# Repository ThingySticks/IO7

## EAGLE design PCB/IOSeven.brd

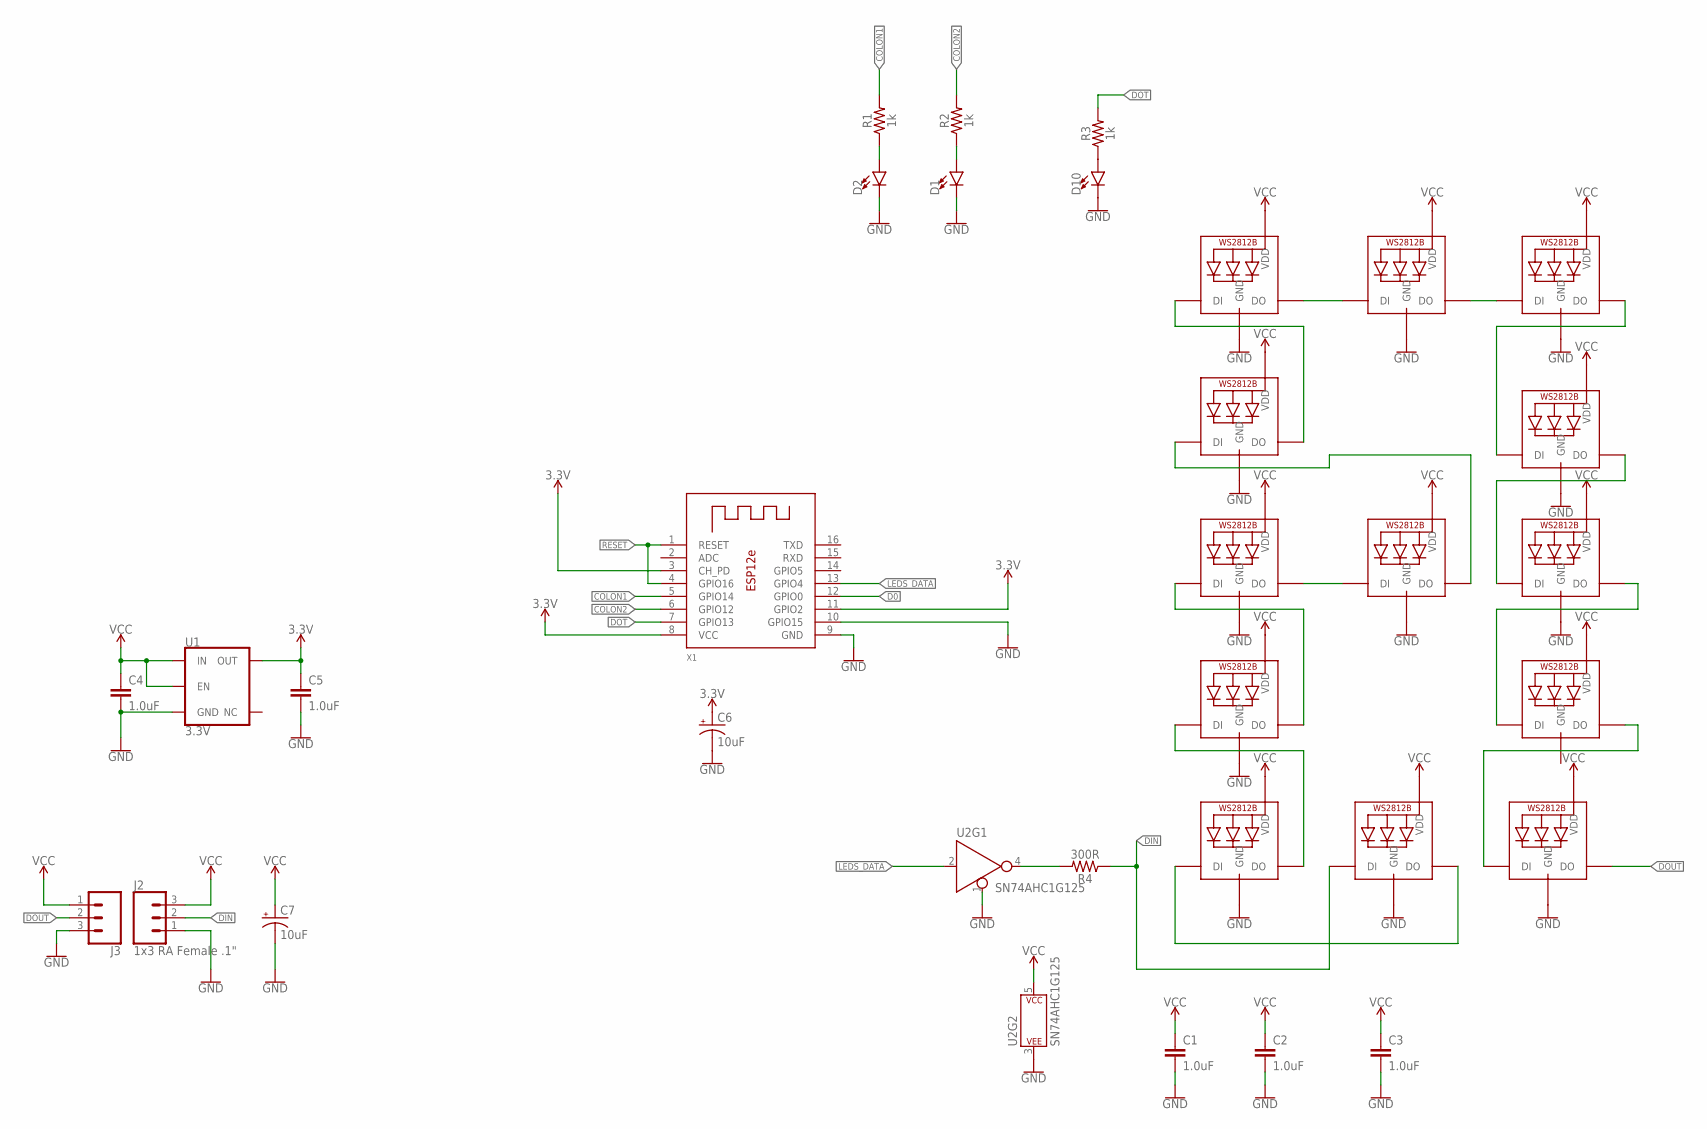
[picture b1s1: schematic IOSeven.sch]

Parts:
C1, C2, C3, C4, C5: 1.0uF; 0603
C6, C7: 10uF; 0603-POLAR
D1, D2, D10: LED0603; LED-0603
J2: 1x3 RA Female .1"; 1X03_SMD_RA_FEMALE
J3: CONN_03SMD_RA_MALE; 1X03_SMD_RA_MALE
LED17, LED18, LED19, LED20, LED21, LED22, LED23, LED24, LED25, LED26, LED27, LED28, LED29: WS2812B3535; LED3535
R1, R2, R3: 1k; 0603
R4: 300R; 0603
U1: 3.3V; SOT23-5
U2: SN74AHC1G125; SOT23-5
X1: ESP-12E

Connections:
3.3V: C5.1, C6.+, U1.5 (OUT), X1.3 (CH_PD), X1.8 (VCC), X1.11 (GPIO2)
COLON1: R1.2, X1.5 (GPIO14)
COLON2: R2.2, X1.6 (GPIO12)
D0: X1.12 (GPIO0)
DIN: J2.2, LED28.1 (DI), R4.1
DOT: R3.2, X1.7 (GPIO13)
DOUT: J3.2, LED27.3 (DO)
GND: C1.2, C2.2, C3.2, C4.2, C5.2, C6.-, C7.-, D1.C, D2.C, D10.C, J2.1, J3.3, LED17.4 (GND), LED18.4 (GND), LED19.4 (GND), LED20.4 (GND), LED21.4 (GND), LED22.4 (GND), LED23.4 (GND), LED24.4 (GND), LED25.4 (GND), LED26.4 (GND), LED27.4 (GND), LED28.4 (GND), LED29.4 (GND), U1.2 (GND), U2.1 (!EN), U2.3 (P$V-), X1.9 (GND), X1.10 (GPIO15)
LEDS_DATA: U2.2 (A), X1.13 (GPIO4)
unnamed: R4.2, U2.4 (Y)
unnamed: LED17.1 (DI), LED28.3 (DO)
unnamed: LED21.3 (DO), LED22.1 (DI)
unnamed: LED20.3 (DO), LED21.1 (DI)
unnamed: D2.A, R1.1
unnamed: D1.A, R2.1
unnamed: D10.A, R3.1
unnamed: LED19.3 (DO), LED29.1 (DI)
unnamed: LED20.1 (DI), LED29.3 (DO)
unnamed: LED18.3 (DO), LED19.1 (DI)
unnamed: LED17.3 (DO), LED18.1 (DI)
unnamed: LED26.3 (DO), LED27.1 (DI)
unnamed: LED25.3 (DO), LED26.1 (DI)
unnamed: LED22.3 (DO), LED23.1 (DI)
unnamed: LED23.3 (DO), LED24.1 (DI)
unnamed: LED24.3 (DO), LED25.1 (DI)
RESET: X1.1 (RESET), X1.4 (GPIO16)
VCC: C1.1, C2.1, C3.1, C4.1, C7.+, J2.3, J3.1, LED17.2 (VDD), LED18.2 (VDD), LED19.2 (VDD), LED20.2 (VDD), LED21.2 (VDD), LED22.2 (VDD), LED23.2 (VDD), LED24.2 (VDD), LED25.2 (VDD), LED26.2 (VDD), LED27.2 (VDD), LED28.2 (VDD), LED29.2 (VDD), U1.1 (IN), U1.3 (EN), U2.5 (P$V+)

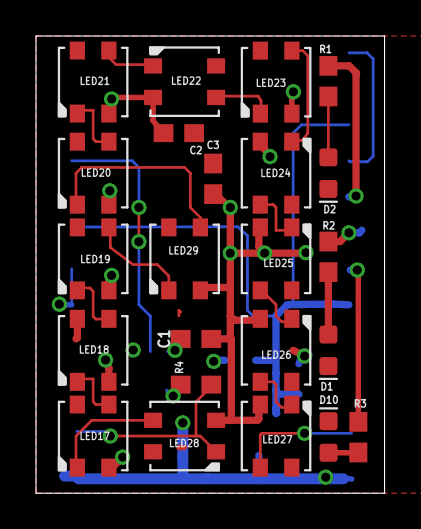
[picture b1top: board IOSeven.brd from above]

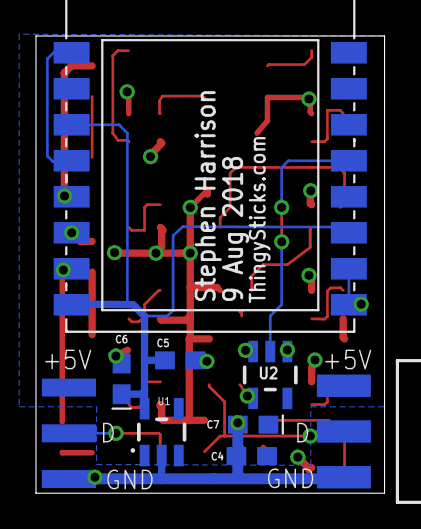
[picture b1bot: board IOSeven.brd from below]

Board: 2 copper layers, 19.4 x 25.4 mm, 32 parts (9 on the bottom side), 26 nets.

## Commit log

2018-09-13 Initial version as sent to OSHPark.

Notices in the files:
parts and their libraries:
SparkFun-LED: Licensing: Creative Commons ShareAlike 4.0 International - https://creativecommons.org/licenses/by-sa/4.0
